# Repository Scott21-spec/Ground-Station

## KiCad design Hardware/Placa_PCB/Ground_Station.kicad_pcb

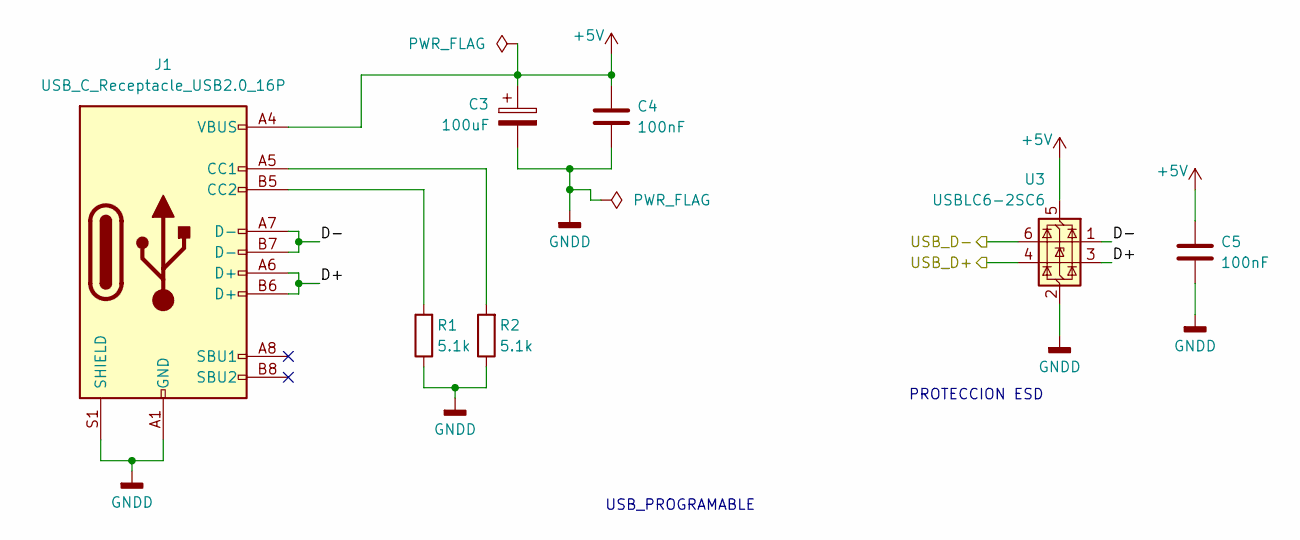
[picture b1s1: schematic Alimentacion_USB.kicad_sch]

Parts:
C3: 100uF; CP_Elec_6.3x5.4
C4, C5: 100nF; C_0805_2012Metric_Pad1.18x1.45mm_HandSolder
J1: USB_C_Receptacle_USB2.0_16P; USB_C_Receptacle_HRO_TYPE-C-31-M-12
R1, R2: 5.1k; R_0805_2012Metric_Pad1.20x1.40mm_HandSolder
U3: USBLC6-2SC6; SOT-23-6

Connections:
+5V: C3.1, C4.1, C5.1, J1.A4 (VBUS), J1.A9 (VBUS), J1.B4 (VBUS), J1.B9 (VBUS), U3.5 (VBUS); also elsewhere on the board
/Alimentacion + USB/D+: J1.A6 (D+), J1.B6 (D+), U3.3 (I/O2)
/Alimentacion + USB/D-: J1.A7 (D-), J1.B7 (D-), U3.1 (I/O1)
/Alimentacion + USB/USB_D+: U3.4 (I/O2); also elsewhere on the board
/Alimentacion + USB/USB_D-: U3.6 (I/O1); also elsewhere on the board
GNDD: C3.2, C4.2, C5.2, J1.A1 (GND), J1.A12 (GND), J1.B1 (GND), J1.B12 (GND), J1.S1 (SHIELD), R1.1, R2.1, U3.2 (GND); also elsewhere on the board
unnamed: J1.A5 (CC1), R2.2
unnamed: J1.B5 (CC2), R1.2

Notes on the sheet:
PROTECCION ESD
USB_PROGRAMABLE

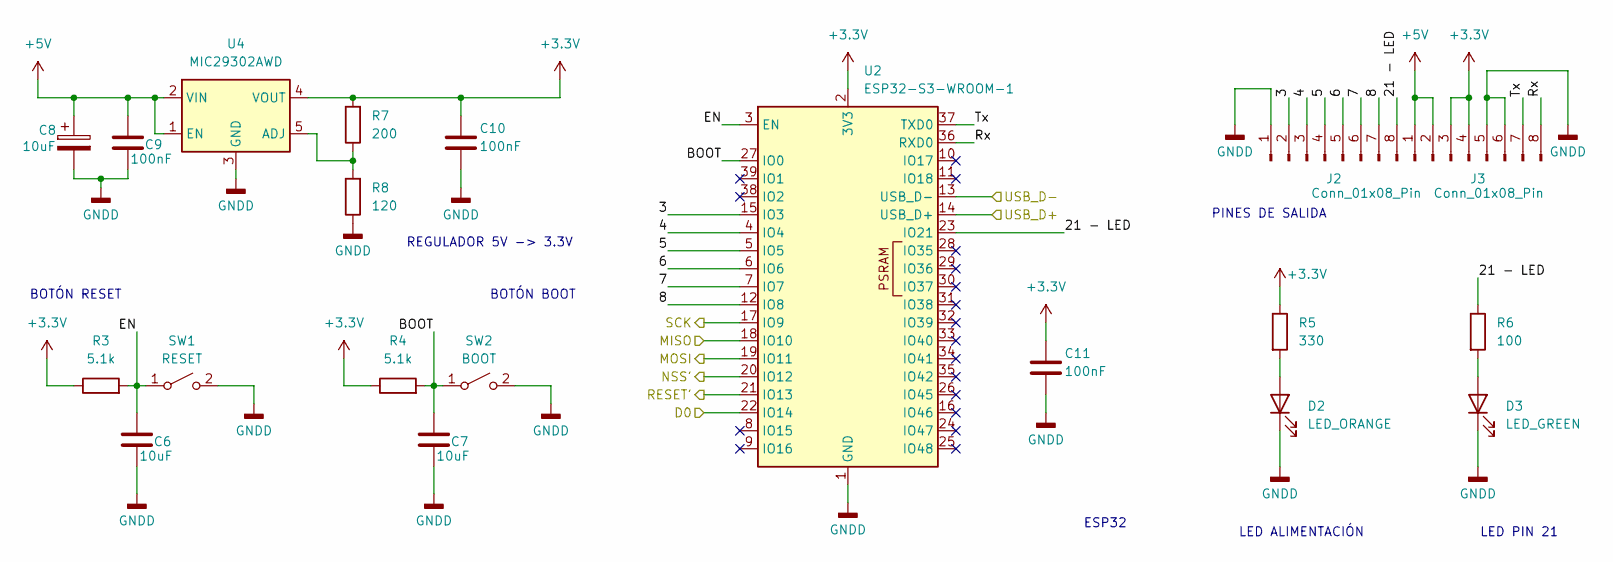
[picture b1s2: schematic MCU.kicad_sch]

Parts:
C6, C7: 10uF; C_0805_2012Metric_Pad1.18x1.45mm_HandSolder
C8: 10uF; CP_Elec_4x5.4
C9, C10, C11: 100nF; C_0805_2012Metric_Pad1.18x1.45mm_HandSolder
D2: LED_ORANGE; LED_0805_2012Metric_Pad1.15x1.40mm_HandSolder
D3: LED_GREEN; LED_0805_2012Metric_Pad1.15x1.40mm_HandSolder
J2, J3: Conn_01x08_Pin; PinSocket_1x08_P2.54mm_Vertical
R3, R4: 5.1k; R_0805_2012Metric_Pad1.20x1.40mm_HandSolder
R5: 330; R_0805_2012Metric_Pad1.20x1.40mm_HandSolder
R6: 100; R_0805_2012Metric_Pad1.20x1.40mm_HandSolder
R7: 200; R_0805_2012Metric_Pad1.20x1.40mm_HandSolder
R8: 120; R_0805_2012Metric_Pad1.20x1.40mm_HandSolder
SW1: RESET; SW_Push_1P1T_NO_E-Switch_TL3301NxxxxxG
SW2: BOOT; SW_Push_1P1T_NO_E-Switch_TL3301NxxxxxG
U2: ESP32-S3-WROOM-1
U4: MIC29302AWD; TO-252-5_TabPin3

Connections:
+3.3V: C10.1, C11.1, J3.3, J3.4, R3.1, R4.1, R5.1, R7.2, U2.2 (3V3), U4.4 (VOUT); also elsewhere on the board
+5V: C8.1, C9.1, J3.1, J3.2, U4.1 (EN), U4.2 (VIN); also elsewhere on the board
/Alimentacion + USB/USB_D+: U2.14 (USB_D+); also elsewhere on the board
/Alimentacion + USB/USB_D-: U2.13 (USB_D-); also elsewhere on the board
/LoRa/D0: U2.22 (IO14); also elsewhere on the board
/LoRa/MISO: U2.18 (IO10); also elsewhere on the board
/LoRa/MOSI: U2.19 (IO11); also elsewhere on the board
/LoRa/NSS': U2.20 (IO12); also elsewhere on the board
/LoRa/RESET': U2.21 (IO13); also elsewhere on the board
/LoRa/SCK: U2.17 (IO9); also elsewhere on the board
/MCU/3: J2.2, U2.15 (IO3)
/MCU/4: J2.3, U2.4 (IO4)
/MCU/5: J2.4, U2.5 (IO5)
/MCU/6: J2.5, U2.6 (IO6)
/MCU/7: J2.6, U2.7 (IO7)
/MCU/8: J2.7, U2.12 (IO8)
/MCU/21 - LED: J2.8, R6.1, U2.23 (IO21)
/MCU/BOOT: C7.1, R4.2, SW2.1 (A), U2.27 (IO0)
/MCU/EN: C6.1, R3.2, SW1.1 (A), U2.3 (EN)
/MCU/Rx: J3.8, U2.36 (RXD0)
/MCU/Tx: J3.7, U2.37 (TXD0)
GNDD: C6.2, C7.2, C8.2, C9.2, C10.2, C11.2, D2.1 (K), D3.1 (K), J2.1, J3.5, J3.6, R8.1, SW1.2 (B), SW2.2 (B), U2.1 (GND), U2.40 (GND), U2.41 (GND), U4.3 (GND); also elsewhere on the board
unnamed: D2.2 (A), R5.2
unnamed: D3.2 (A), R6.2
unnamed: R7.1, R8.2, U4.5 (ADJ)

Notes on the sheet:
LED ALIMENTACIÓN
BOTÓN RESET
ESP32
BOTÓN BOOT
REGULADOR 5V -> 3.3V
LED PIN 21
PINES DE SALIDA

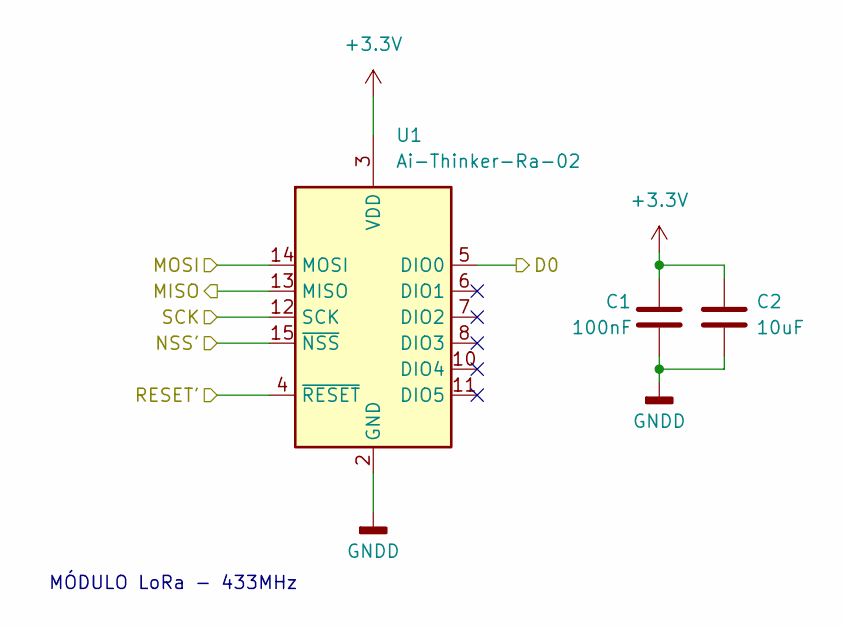
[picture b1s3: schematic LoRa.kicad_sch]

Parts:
C1: 100nF; C_0805_2012Metric_Pad1.18x1.45mm_HandSolder
C2: 10uF; C_0805_2012Metric_Pad1.18x1.45mm_HandSolder
U1: Ai-Thinker-Ra-02; Ai-Thinker-Ra-01-LoRa

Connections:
+3.3V: C1.1, C2.1, U1.3 (VDD); also elsewhere on the board
/LoRa/D0: U1.5 (DIO0); also elsewhere on the board
/LoRa/MISO: U1.13 (MISO); also elsewhere on the board
/LoRa/MOSI: U1.14 (MOSI); also elsewhere on the board
/LoRa/NSS': U1.15 (~NSS); also elsewhere on the board
/LoRa/RESET': U1.4 (~RESET); also elsewhere on the board
/LoRa/SCK: U1.12 (SCK); also elsewhere on the board
GNDD: C1.2, C2.2, U1.1 (GND), U1.2 (GND), U1.9 (GND), U1.16 (GND); also elsewhere on the board

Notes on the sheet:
MÓDULO LoRa - 433MHz

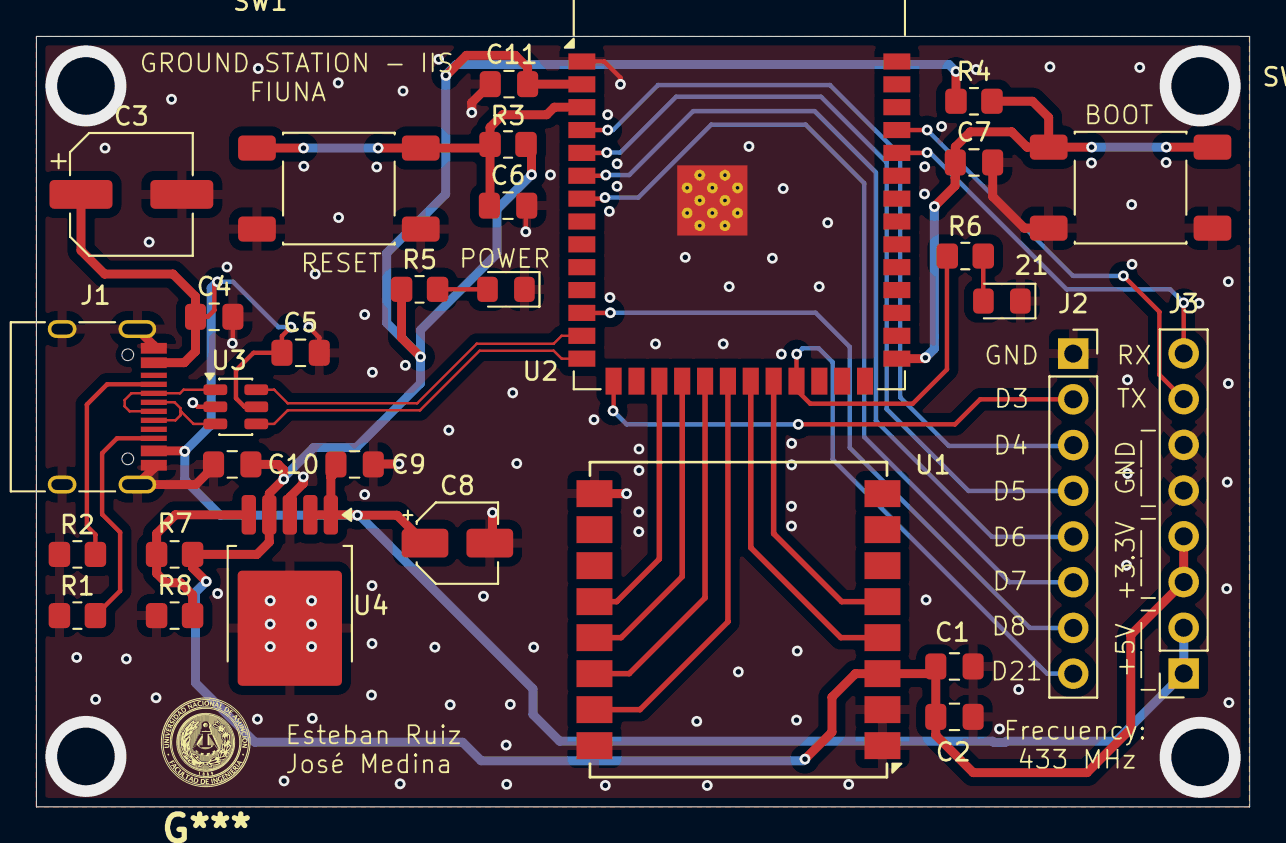
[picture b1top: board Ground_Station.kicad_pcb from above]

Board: 4 copper layers, 67.4 x 42.8 mm, 30 parts (0 on the bottom side), 29 nets.

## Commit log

2026-02-24 Create Lista_Componentes
2026-03-10 Rename Lista_Componentes to Lista_Componentes.txt
2026-03-19 Subimos el logo dentro de la carpeta Hardware
2026-03-19 Agregando logo
2026-03-19 Agregando el esquematico completo y el PCB con los componentes ordenados
2026-03-21 Agregando el PCB terminado
2026-03-30 Cambios
2026-04-02 Ningun cambio
2026-04-28 Placa Final
2026-04-29 Actualizacion PCB
